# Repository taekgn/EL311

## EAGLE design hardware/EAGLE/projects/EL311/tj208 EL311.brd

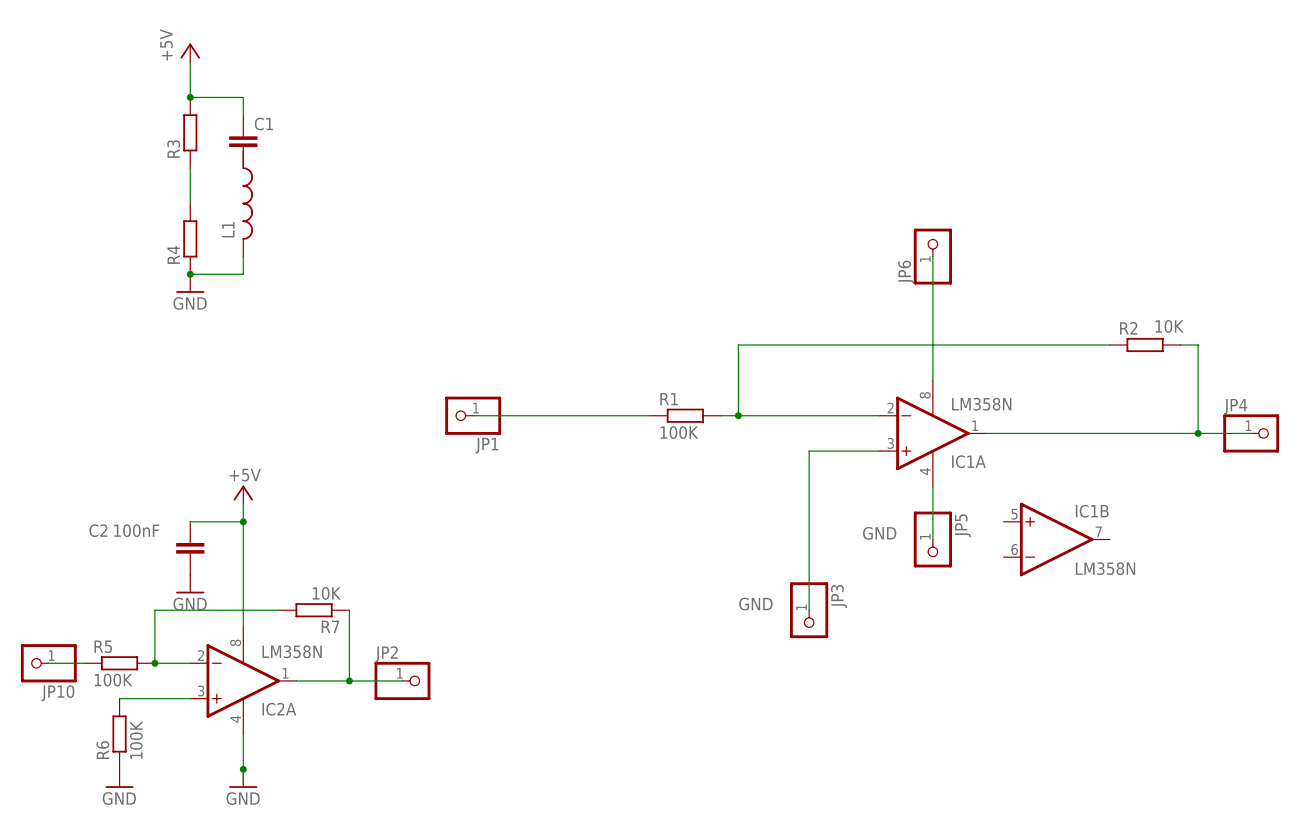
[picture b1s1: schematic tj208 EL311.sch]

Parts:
C1: C-EU025-024X044; C025-024X044
C2: 100nF; C025-024X044
IC1, IC2: LM358N; DIL08
JP1, JP2, JP3, JP4, JP5, JP6, JP10: PINHD-1X1; 1X01
L1: L-US0204/5; 0204/5
R1, R5: 100K; 0207/10
R2: 10K; 0207/10
R3, R4: R-EU_0207/5V; 0207/5V
R6: 100K; 0207/5V
R7: 10K; 0207/5V

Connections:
GND: C2.2, IC1.3 (+IN), IC1.4 (V-), IC2.3 (+IN), IC2.4 (V-), JP3.1, JP5.1, L1.2, R4.1, R6.1, R6.2
unnamed: JP1.1, R1.1
unnamed: IC1.2 (-IN), R1.2, R2.1
unnamed: IC1.8 (V+), JP6.1
unnamed: R3.1, R4.2
unnamed: IC2.1 (OUT), JP2.1, R7.1
unnamed: IC1.1 (OUT), JP4.1, R2.2
unnamed: IC2.2 (-IN), R5.2, R7.2
unnamed: JP10.1, R5.1
VCC: C1.1, C2.1, IC2.8 (V+), R3.2

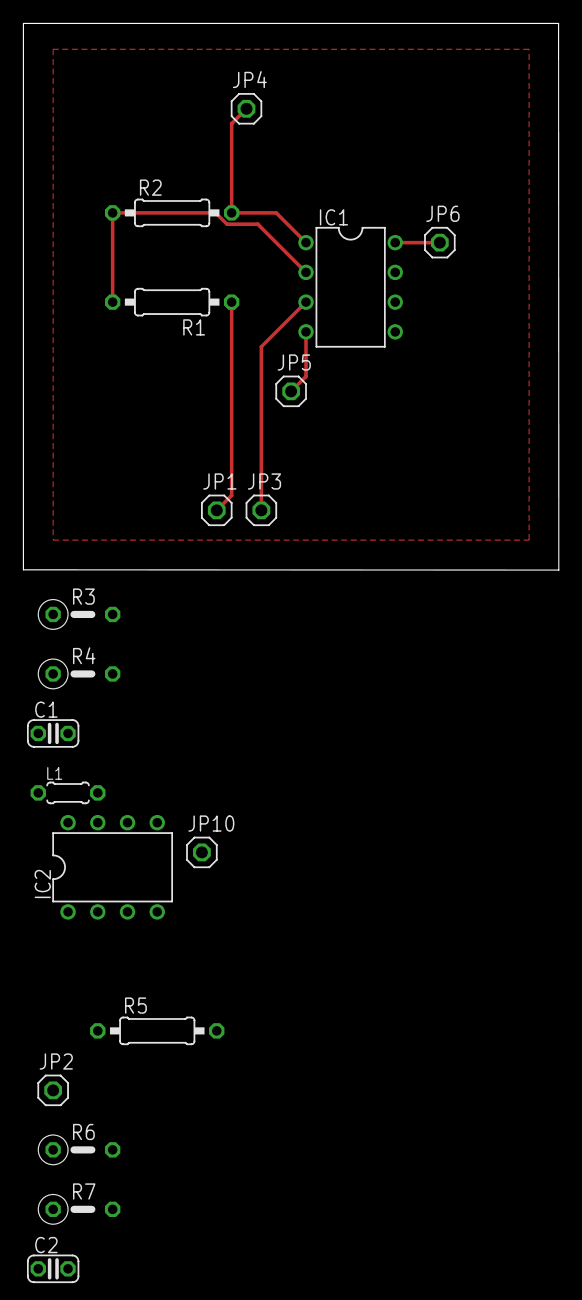
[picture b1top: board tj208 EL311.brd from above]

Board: 2 copper layers, 45.7 x 46.7 mm, 19 parts (0 on the bottom side), 10 nets.

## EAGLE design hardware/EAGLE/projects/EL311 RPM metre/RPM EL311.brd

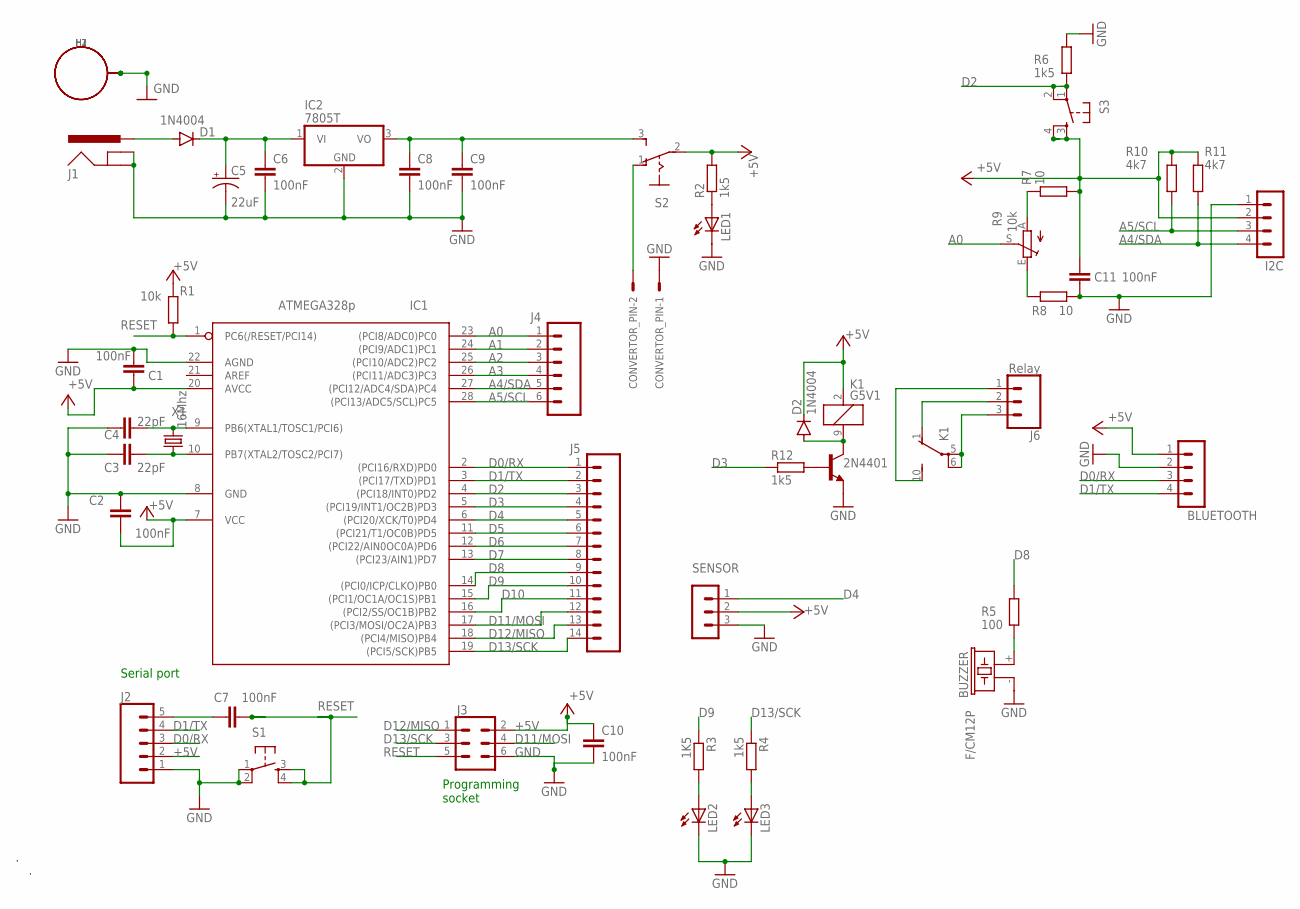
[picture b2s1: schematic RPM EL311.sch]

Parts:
2N4401: NPN_TRANSISTOR2N3904TO92-EBC; TO92-EBC
BLUETOOTH: MA04-1
BUZZER: F/CM12P
C1, C2, C6, C7, C8, C9, C10, C11: 100nF; C2.5-2
C3, C4: 22pF; C2.5-2
C5: 22uF; E2,5-7
CONVERTOR_PIN: 5V; CON-MOLEX_6410-02
D1, D2: 1N4004; DO41-10
H1, H2, H3: STANDOFF_ELECTRICAL; STANDOFF-ELECTRICAL
I2C: MA04-1
IC1: ATMEGA328p; DIL28-3
IC2: 7805T; TO220H
J1: EL311-ROBOT_SPARKFUN-CONNECTORS_POWER_JACKPTH; EL311-ROBOT_SPARKFUN-CONNECTORS_POWER_JACK_PTH
J2: CONN_05; 1X05
J3: FEMALE 2x3; 2X3-SHROUDED
J4: CONN_06SILK_FEMALE_PTH; 1X06
J5: CONN_14; 1X14
J6: Relay; 1X03_LONGPADS
K1: G5V1
LED1: LED3MM
LED2, LED3: LED3MM:1; LED3MM
R1: 10k; 0207/10
R2, R4, R6, R12: 1k5; 0207/10
R3: 1K5; 0207/10
R5: 100; 0207/10
R7, R8: 10; 0207/10
R9: 10k; POT_RS3
R10, R11: 4k7; 0207/10
S1, S3: EL311-ROBOT_SPARKFUN-ELECTROMECHANICAL_TAC_SWITCH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; EL311-ROBOT_SPARKFUN-ELECTROMECHANICAL_TACTILE-PTH
S2: SWITCH_M251
SENSOR: MA03-1
X1: 16Mhz; HC49U-V

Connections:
0V: R8.1, R9.E
5V: R7.1, R9.A
+5V: BLUETOOTH.1, C1.2, C2.2, C10.1, C11.1, D2.C, I2C.2, IC1.7 (VCC), IC1.20 (AVCC), J2.2, J3.2, K1.2 (1), R1.1, R2.2, R7.2, R10.1, R11.1, S2.2, S3.3, S3.4, SENSOR.2
A0: IC1.23 ((PCI8/ADC0)PC0), J4.1, R9.S
A1: IC1.24 ((PCI9/ADC1)PC1), J4.2
A2: IC1.25 ((PCI10/ADC2)PC2), J4.3
A3: IC1.26 ((PCI11/ADC3)PC3), J4.4
A4/SDA: I2C.4, IC1.27 ((PCI12/ADC4/SDA)PC4), J4.5, R11.2
A5/SCL: I2C.3, IC1.28 ((PCI13/ADC5/SCL)PC5), J4.6, R10.2
CONVERTOR: CONVERTOR_PIN.2, S2.1 (O)
D0/RX: BLUETOOTH.3, IC1.2 ((PCI16/RXD)PD0), J2.3, J5.1
D1/TX: BLUETOOTH.4, IC1.3 ((PCI17/TXD)PD1), J2.4, J5.2
D2: IC1.4 ((PCI18/INT0)PD2), J5.3, R6.2, S3.1, S3.2
D3: IC1.5 ((PCI19/INT1/OC2B)PD3), J5.4, R12.1
D4: IC1.6 ((PCI20/XCK/T0)PD4), J5.5, SENSOR.1
D5: IC1.11 ((PCI21/T1/OC0B)PD5), J5.6
D6: IC1.12 ((PCI22/AIN0OC0A)PD6), J5.7
D7: IC1.13 ((PCI23/AIN1)PD7), J5.8
D8: IC1.14 ((PCI0/ICP/CLKO)PB0), J5.9, R5.1
D9: IC1.15 ((PCI1/OC1A/OC1S)PB1), J5.10, R3.1
D10: IC1.16 ((PCI2/SS/OC1B)PB2), J5.11
D11/MOSI: IC1.17 ((PCI3/MOSI/OC2A)PB3), J3.4, J5.12
D12/MISO: IC1.18 ((PCI4/MISO)PB4), J3.1, J5.13
D13/SCK: IC1.19 ((PCI5/SCK)PB5), J3.3, J5.14, R4.1
GND: 2N4401.E, BLUETOOTH.2, BUZZER.- (2), C1.1, C2.1, C3.1, C4.1, C5.-, C6.2, C8.2, C9.2, C10.2, C11.2, CONVERTOR_PIN.1, H1.P1, H2.P1, H3.P1, I2C.1, IC1.8 (GND), IC1.22 (AGND), IC2.2 (GND), J1.GND, J1.GNDBREAK, J2.1, J3.6, LED1.K (C), LED2.K (C), LED3.K (C), R6.1, R8.2, S1.1, S1.2, SENSOR.3
LED2: LED2.A, R3.2
LED3: LED3.A, R4.2
unnamed: J6.1, K1.10 (S)
unnamed: C3.2, IC1.10 (PB7(XTAL2/TOSC2/PCI7)), X1.1
unnamed: C4.2, IC1.9 (PB6(XTAL1/TOSC1/PCI6)), X1.2
unnamed: LED1.A, R2.1
unnamed: C7.1, J2.5
unnamed: J6.2, K1.1 (O)
unnamed: J6.3, K1.5, K1.6
unnamed: 2N4401.C, D2.A, K1.9 (2)
unnamed: 2N4401.B, R12.2
PWR3: D1.A, J1.PWR
PWR4: C5.+, C6.1, D1.C, IC2.1 (VI)
R5: BUZZER.+ (1), R5.2
REGULATOR: C8.1, C9.1, IC2.3 (VO), S2.3 (S)
RESET: C7.2, IC1.1 (PC6(/RESET/PCI14)), J3.5, R1.2, S1.3, S1.4

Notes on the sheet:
Programming socket
Serial port

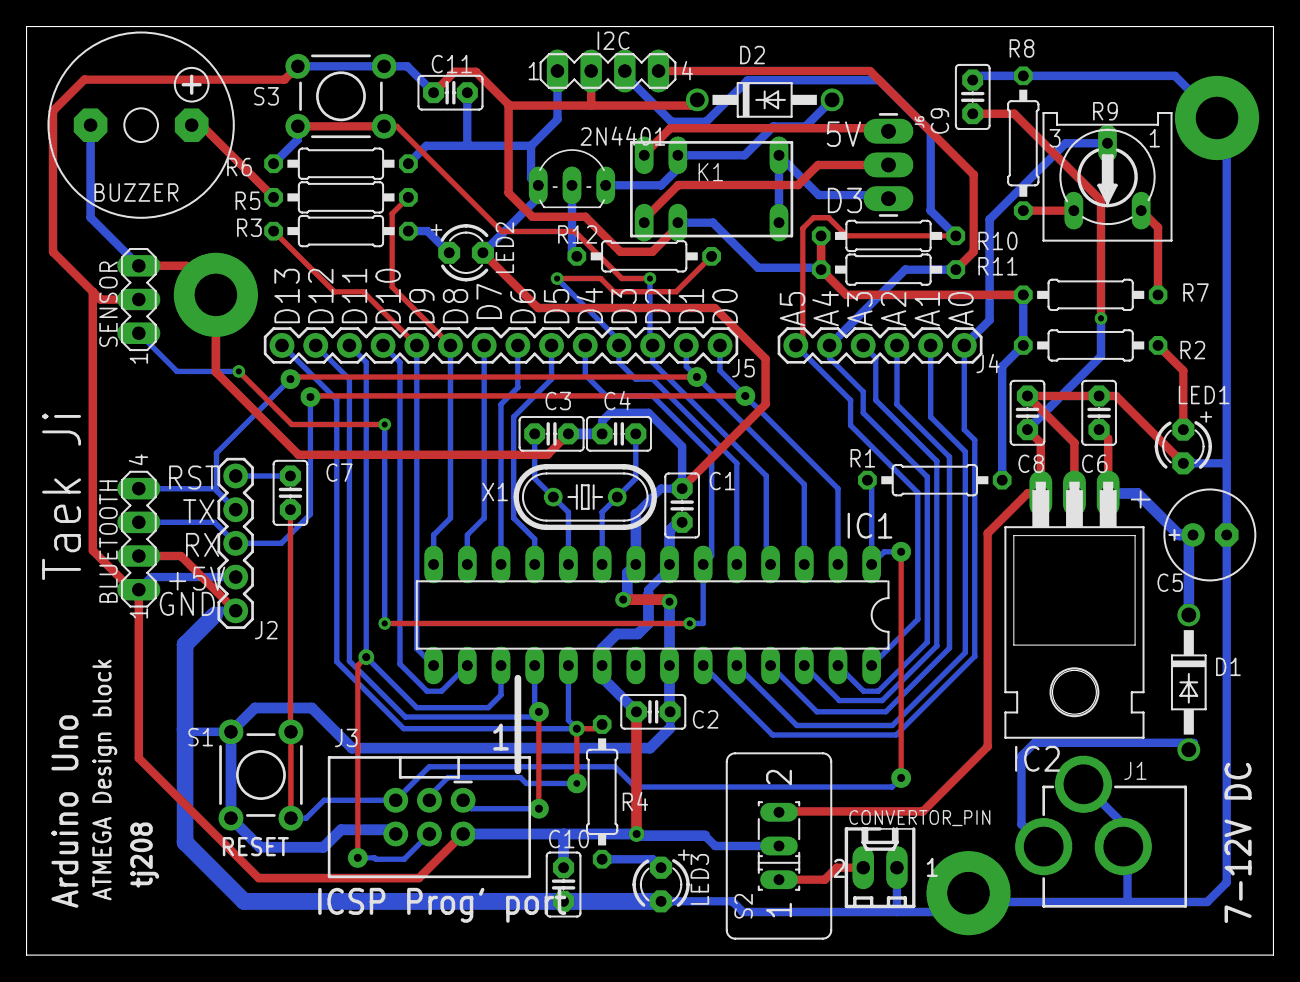
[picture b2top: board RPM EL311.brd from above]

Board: 2 copper layers, 94.0 x 70.0 mm, 50 parts (0 on the bottom side), 41 nets.

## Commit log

2020-12-26 Retrying
2020-12-26 hardware
2020-12-26 hardware files
2020-12-26 remove

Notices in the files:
parts and their libraries:
SparkFun-Connectors: Licensing: Creative Commons ShareAlike 4.0 International - https://creativecommons.org/licenses/by-sa/4.0
